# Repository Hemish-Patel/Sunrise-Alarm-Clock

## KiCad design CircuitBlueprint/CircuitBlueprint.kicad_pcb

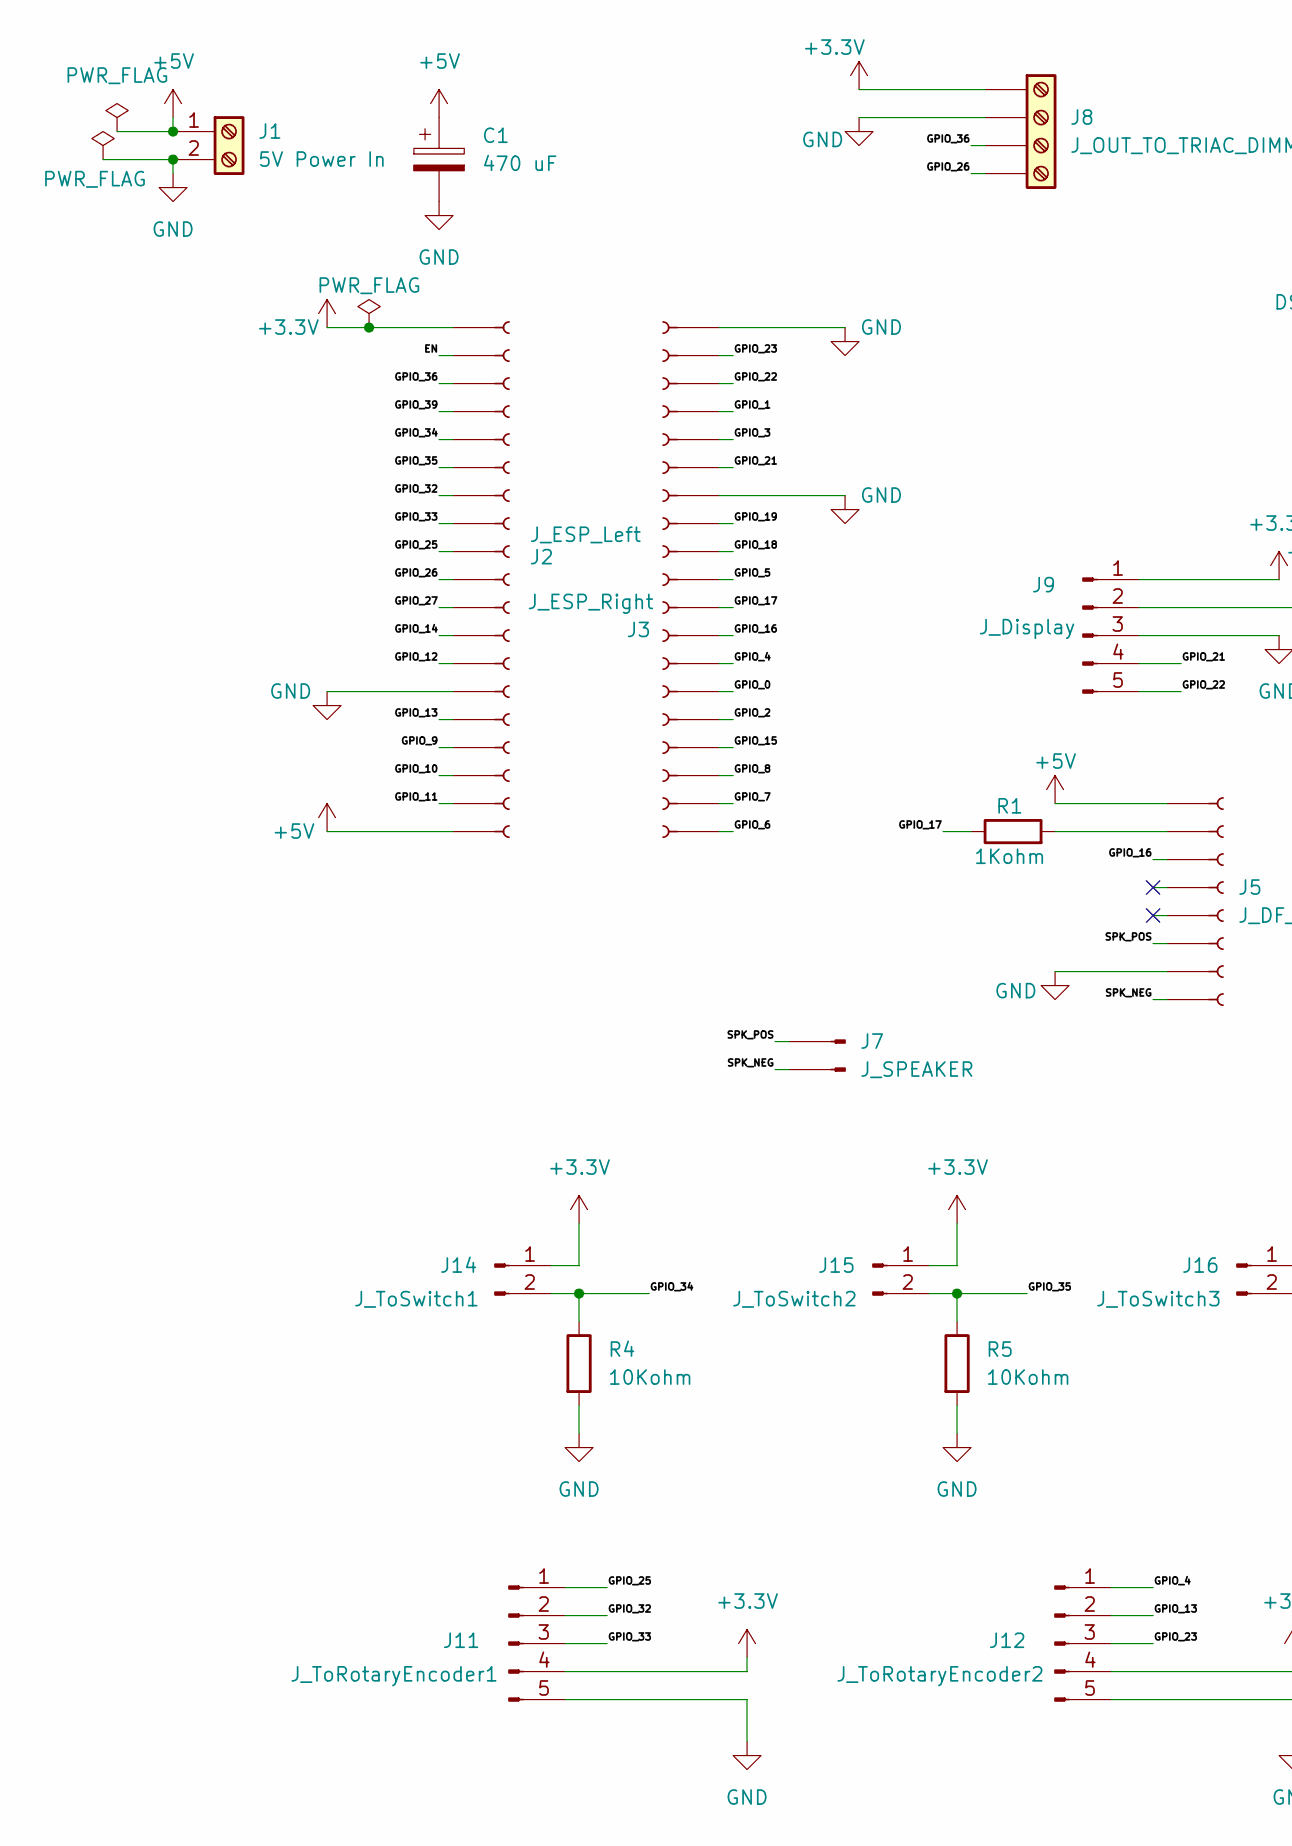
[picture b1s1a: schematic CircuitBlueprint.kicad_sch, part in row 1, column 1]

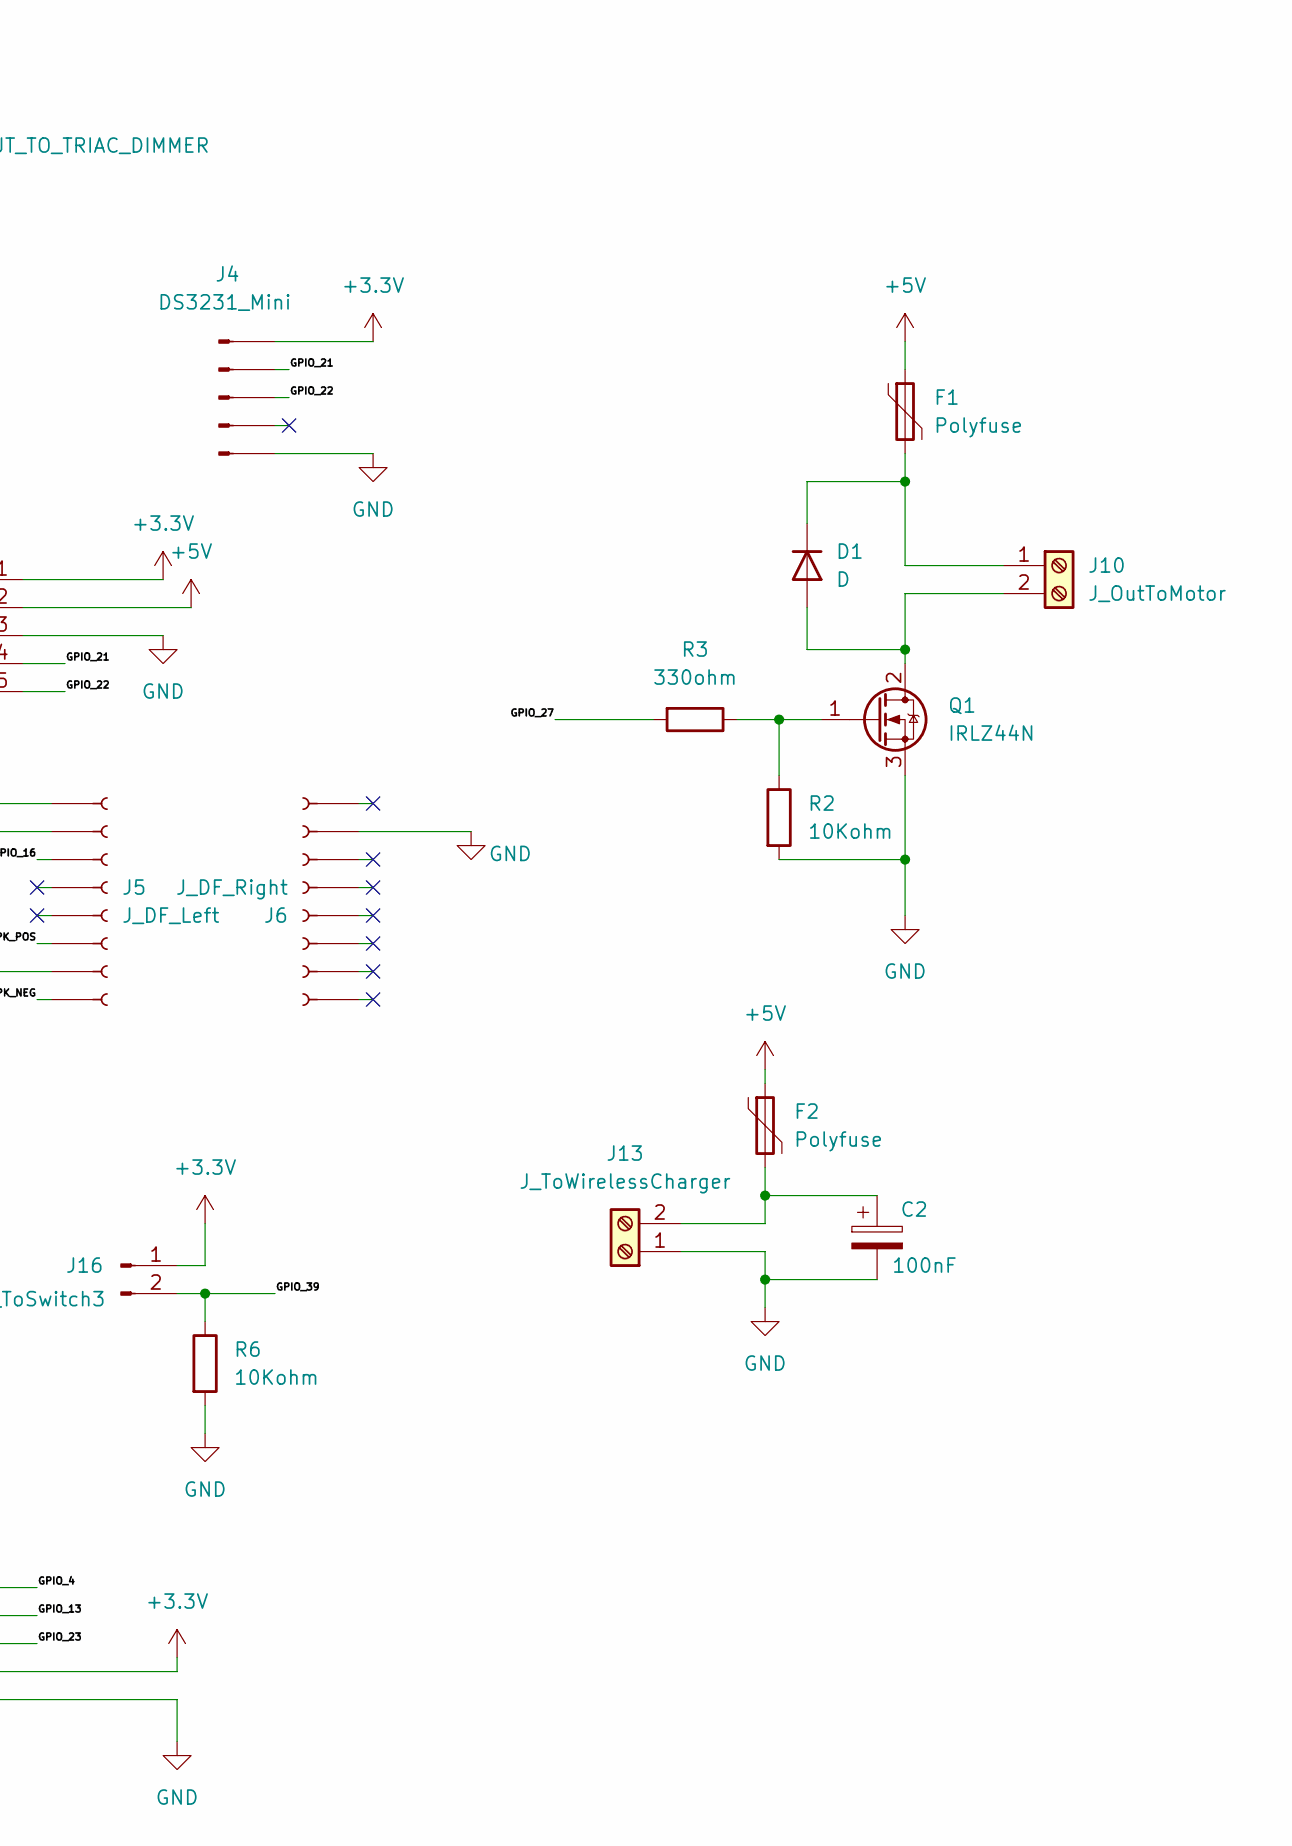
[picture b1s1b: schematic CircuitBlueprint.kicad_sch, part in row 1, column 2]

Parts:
C1: 470 uF; CP_Radial_D8.0mm_P3.80mm
C2: 100nF; C_Disc_D4.7mm_W2.5mm_P5.00mm
D1: D; D_DO-41_SOD81_P7.62mm_Horizontal
F1, F2: Polyfuse; Fuse_Bourns_MF-RG500
J1: 5V Power In; TerminalBlock_Phoenix_MKDS-1,5-2_1x02_P5.00mm_Horizontal
J2: J_ESP_Left; PinSocket_1x19_P2.54mm_Vertical
J3: J_ESP_Right; PinSocket_1x19_P2.54mm_Vertical
J4: DS3231_Mini; PinHeader_1x05_P2.54mm_Vertical
J5: J_DF_Left; PinSocket_1x08_P2.54mm_Vertical
J6: J_DF_Right; PinSocket_1x08_P2.54mm_Vertical
J7: J_SPEAKER; PinHeader_1x02_P2.54mm_Vertical
J8: J_OUT_TO_TRIAC_DIMMER; PinHeader_1x04_P2.54mm_Vertical
J9: J_Display; PinHeader_1x05_P2.54mm_Vertical
J10: J_OutToMotor; TerminalBlock_Phoenix_MKDS-1,5-2_1x02_P5.00mm_Horizontal
J11: J_ToRotaryEncoder1; PinHeader_1x05_P2.54mm_Vertical
J12: J_ToRotaryEncoder2; PinHeader_1x05_P2.54mm_Vertical
J13: J_ToWirelessCharger; TerminalBlock_Phoenix_MKDS-1,5-2_1x02_P5.00mm_Horizontal
J14: J_ToSwitch1; PinHeader_1x02_P2.54mm_Vertical
J15: J_ToSwitch2; PinHeader_1x02_P2.54mm_Vertical
J16: J_ToSwitch3; PinHeader_1x02_P2.54mm_Vertical
Q1: IRLZ44N; TO-220-3_Vertical
R1: 1Kohm; R_Axial_DIN0207_L6.3mm_D2.5mm_P7.62mm_Horizontal
R2, R4, R5, R6: 10Kohm; R_Axial_DIN0207_L6.3mm_D2.5mm_P7.62mm_Horizontal
R3: 330ohm; R_Axial_DIN0207_L6.3mm_D2.5mm_P7.62mm_Horizontal

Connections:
+3.3V: J2.1, J4.1, J8.1, J9.1, J11.4, J12.4, J14.1, J15.1, J16.1
+5V: C1.1, F1.1, F2.1, J1.1, J2.19, J5.1, J9.2
/EN: J2.2
/GPIO_0: J3.6
/GPIO_1: J3.16
/GPIO_2: J3.5
/GPIO_3: J3.15
/GPIO_4: J3.7, J12.1
/GPIO_5: J3.10
/GPIO_6: J3.1
/GPIO_7: J3.2
/GPIO_8: J3.3
/GPIO_9: J2.16
/GPIO_10: J2.17
/GPIO_11: J2.18
/GPIO_12: J2.13
/GPIO_13: J2.15, J12.2
/GPIO_14: J2.12
/GPIO_15: J3.4
/GPIO_16: J3.8, J5.3
/GPIO_17: J3.9, R1.1
/GPIO_18: J3.11
/GPIO_19: J3.12
/GPIO_21: J3.14, J4.2, J9.4
/GPIO_22: J3.17, J4.3, J9.5
/GPIO_23: J3.18, J12.3
/GPIO_25: J2.9, J11.1
/GPIO_26: J2.10, J8.4
/GPIO_27: J2.11, R3.2
/GPIO_32: J2.7, J11.2
/GPIO_33: J2.8, J11.3
/GPIO_34: J2.5, J14.2, R4.1
/GPIO_35: J2.6, J15.2, R5.1
/GPIO_36: J2.3, J8.3
/GPIO_39: J2.4, J16.2, R6.1
/SPK_NEG: J5.8, J7.1
/SPK_POS: J5.6, J7.2
GND: C1.2, C2.2, J1.2, J2.14, J3.13, J3.19, J4.5, J5.7, J6.7 (Pin_7_7), J8.2, J9.3, J11.5, J12.5, J13.1, Q1.3 (S), R2.2, R4.2, R5.2, R6.2
unnamed: D1.2 (A), J10.2, Q1.2 (D)
unnamed: D1.1 (K), F1.2, J10.1
unnamed: J5.2, R1.2
unnamed: C2.1, F2.2, J13.2
unnamed: Q1.1 (G), R2.1, R3.1

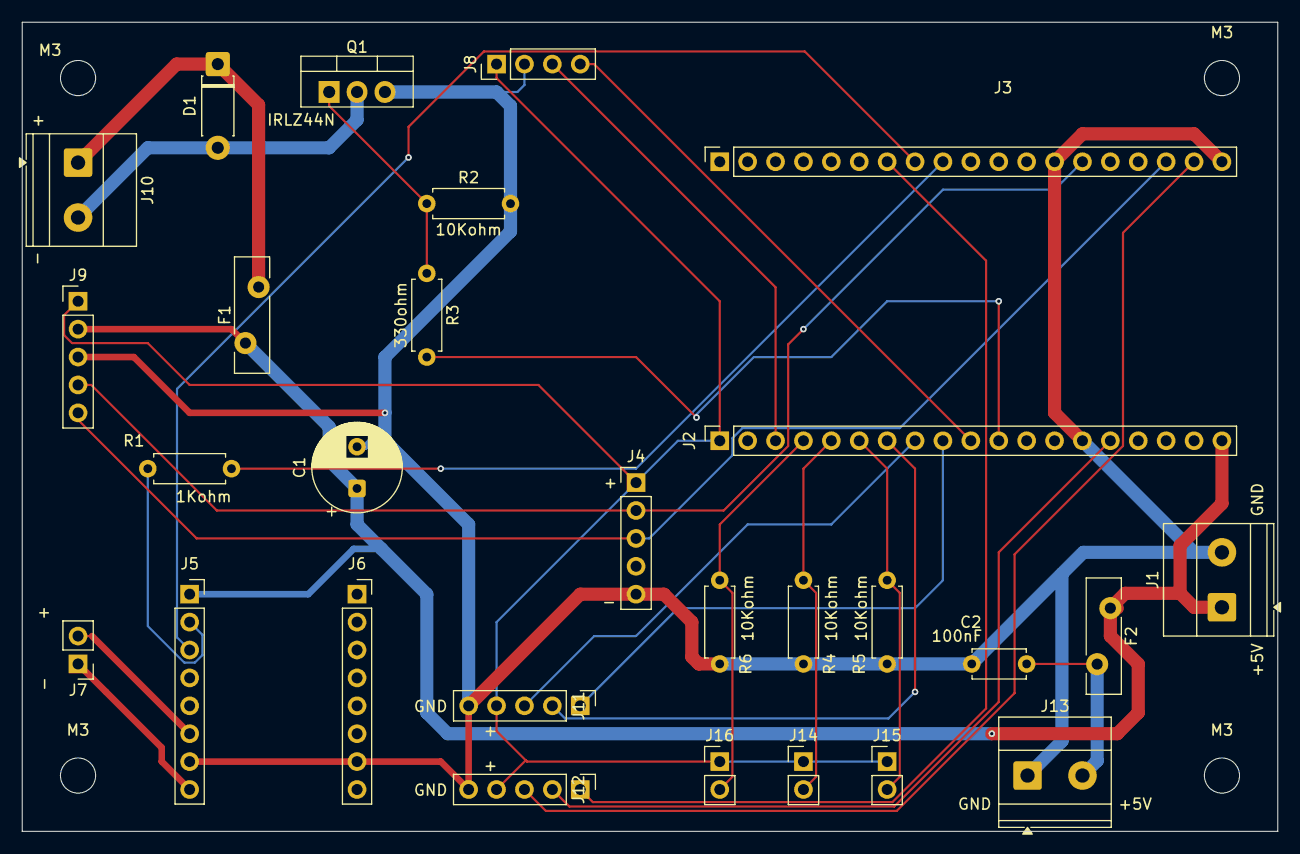
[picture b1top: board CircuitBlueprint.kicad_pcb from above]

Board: 2 copper layers, 114.3 x 73.7 mm, 32 parts (0 on the bottom side), 26 nets.

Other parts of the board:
M3, M3#2, M3#3, M3#4: M3; MountingHole_3.2mm_M3
